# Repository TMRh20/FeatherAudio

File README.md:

# FeatherAudio
Custom Circuit Board for Feather 52840

Designed by TMRh20, Sponsored by [PCBWay](https://pcbway.com)
<br>

<br><br>
Requirements:<br>
2 x Custom Circuit Board <br>
2 x Feather 52840 based board (Feather 52840 Sense or Express) <br>
2 x Max98357A I2S Amplifier breakout <br>
2 x 4 to 8 Ohm Speaker (Gikfun 1.5" 4-Ohm, 3w, EK1794) <br>
2 x 2032 3.3v Coin Battery <br>
6 x AAA Battery <br>
(Optional) 2 x Micro-SD Card <br>
<br>
This custom circuit board was designed for basic prototyping via the AutoAnalogAudio library, however, it can be used
to create a custom walkie-talkie or intercom with range similar to Bluetooth. <br>

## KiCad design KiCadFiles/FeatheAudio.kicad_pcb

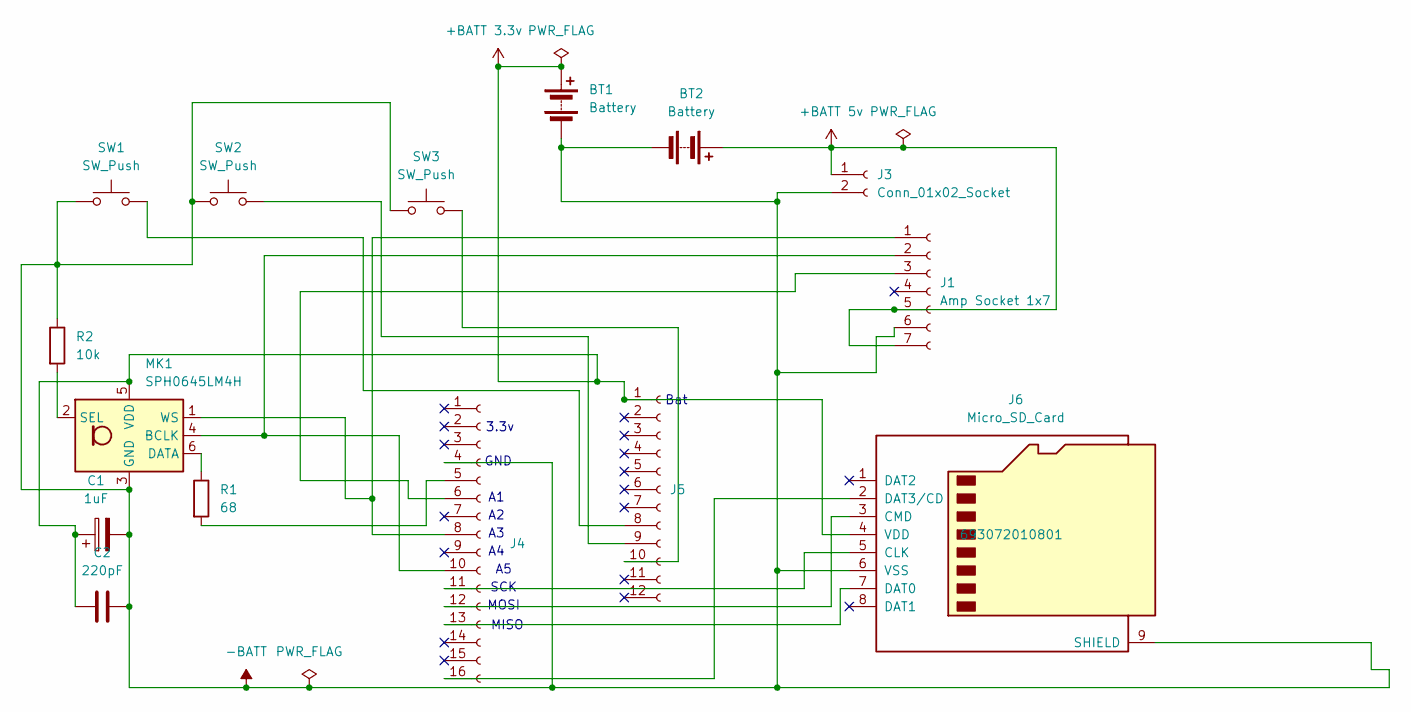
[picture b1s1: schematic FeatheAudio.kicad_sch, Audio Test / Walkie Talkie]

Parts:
BT1: Battery; BatteryHolder_Keystone_1058_1x2032; Part Number 1058
BT2: Battery; BatteryHolder_Keystone_2479_3xAAA; Part Number 2479
C1: 1uF; C_0603_1608Metric; Part Number GRM188D72A105KE01D（100V 1uF X7T 10% 060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
C2: 220pF; CP_EIA-1608-08_AVX-J; Part Number VJ0603A221FXACW1BC
J1: Amp Socket 1x7; PinSocket_1x07_P2.54mm_Vertical; Part Number 61300711821
J3: Conn_01x02_Socket; JST_PH_S2B-PH-K_1x02_P2.00mm_Horizontal; Part Number S2B-PH-K-S(LF)(SN)
J4: XIAO LEFT; PinSocket_1x16_P2.54mm_Vertical_SMD_Pin1Left; Part Number DS1023-16-1*16B81XBX1 work? https://www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
J5: XIAO RIGHT; PinSocket_1x12_P2.54mm_Vertical_SMD_Pin1Left; Part Number 4217-CSHC121-1202A001C1AC-ND https://ww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
J6: Micro_SD_Card; microSD_HC_Hirose_DM3AT-SF-PEJM5; Part Number 693072010801
MK1: SPH0645LM4H; Knowles_SPH0645LM4H-6_3.5x2.65mm; Part Number SPH0645LM4H-1-8
R1: 68; R_0402_1005Metric; Part Number FRC0402J680 TS（68R 5% 62.5mW 0402）
R2: 10k; R_0402_1005Metric; Part Number RC0402FR-0710KL（0402 10K 1%）
SW1, SW2, SW3: SW_Push; SW_Tactile_SPST_Angled_PTS645Vx83-2LFS; Part Number Y97HS12A4VAFP

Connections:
+BATT 3.3v: BT1.1 (+), C1.1, C2.1, J5.1, J6.4 (VDD), MK1.5 (VDD)
+BATT 5v: BT2.1 (+), J1.5, J1.7, J3.1
-BATT: BT1.2 (-), BT2.2 (-), C1.2, C2.2, J1.6, J3.2, J4.4, J6.6 (VSS), J6.9 (SHIELD), MK1.3 (GND), R2.1, SW1.1, SW2.1, SW3.1
unnamed: J1.1, J4.8, MK1.1 (WS)
unnamed: J1.2, J4.10, MK1.4 (BCLK)
unnamed: J1.3, J4.6
unnamed: J4.5, R1.2
unnamed: J4.11, J6.5 (CLK)
unnamed: J4.12, J6.3 (CMD)
unnamed: J4.13, J6.7 (DAT0)
unnamed: J4.16, J6.2 (DAT3/CD)
unnamed: J5.8, SW1.2
unnamed: J5.9, SW2.2
unnamed: J5.10, SW3.2
unnamed: MK1.6 (DATA), R1.1
unnamed: MK1.2 (SEL), R2.2

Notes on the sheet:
3.3v
MISO
SCK
GND
Bat
MOSI

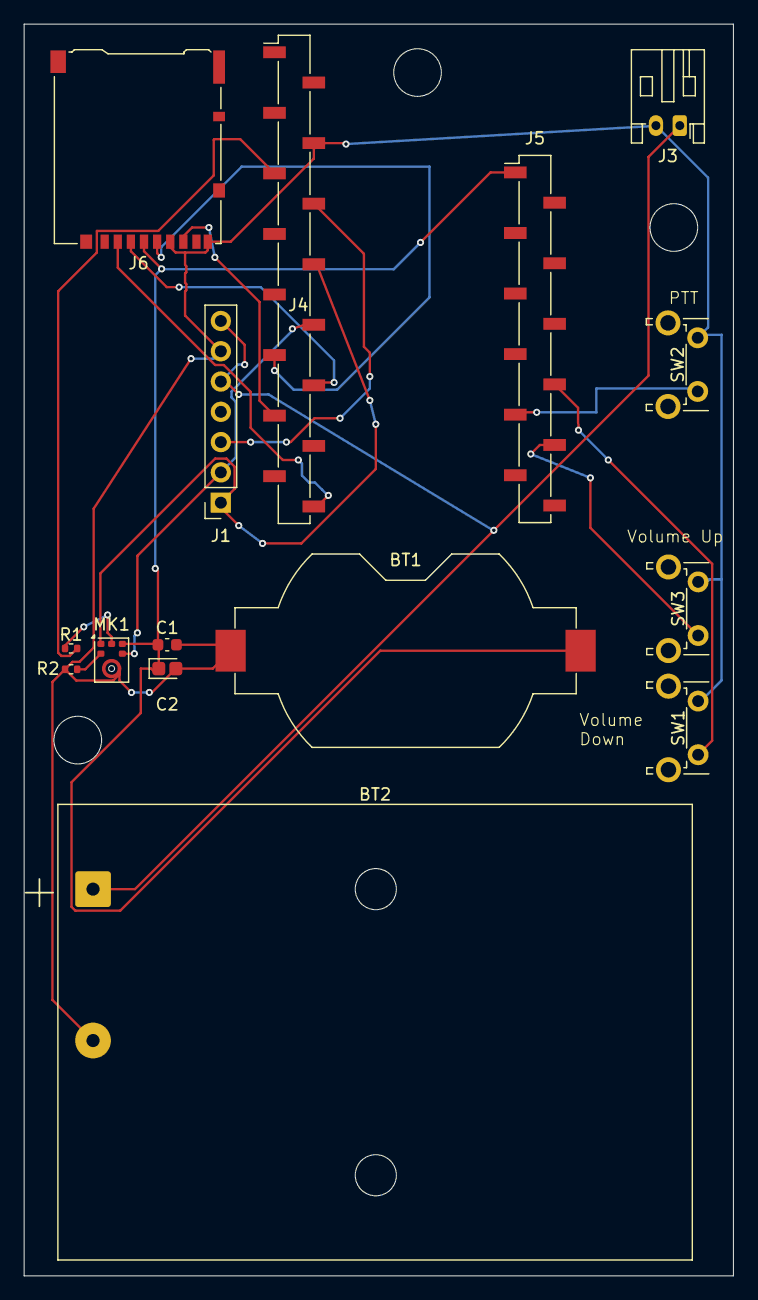
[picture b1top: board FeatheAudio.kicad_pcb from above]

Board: 2 copper layers, 59.5 x 105.0 mm, 15 parts (0 on the bottom side), 16 nets.

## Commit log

2026-02-10 FeatherAudio PCB First Commit
2026-02-11 Update examples
2026-02-13 Add full transceiver example
2026-02-14 Adjust radio rate for better distance
2026-02-15 Update J5 part number & BOM
2026-02-16 Update I2S_TransmitterAndReceiver.ino
    - Cleaner debug prints in the Serial Plotter
    - Disable DAC instead of feeding it 0s
    - Adjust volume control var
2026-02-20 Add v1 3D-Print for base
2026-02-28 Add MP3 player example
2026-02-28 Update MP3 Player example
